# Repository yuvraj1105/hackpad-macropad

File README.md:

# hackpad-macropad
A compact, customizable macropad designed for productivity, shortcuts, and everyday workflow automation. HackPad provides programmable keys that can be mapped to custom shortcuts, commands, macros, and applications, making repetitive tasks faster and more convenient.

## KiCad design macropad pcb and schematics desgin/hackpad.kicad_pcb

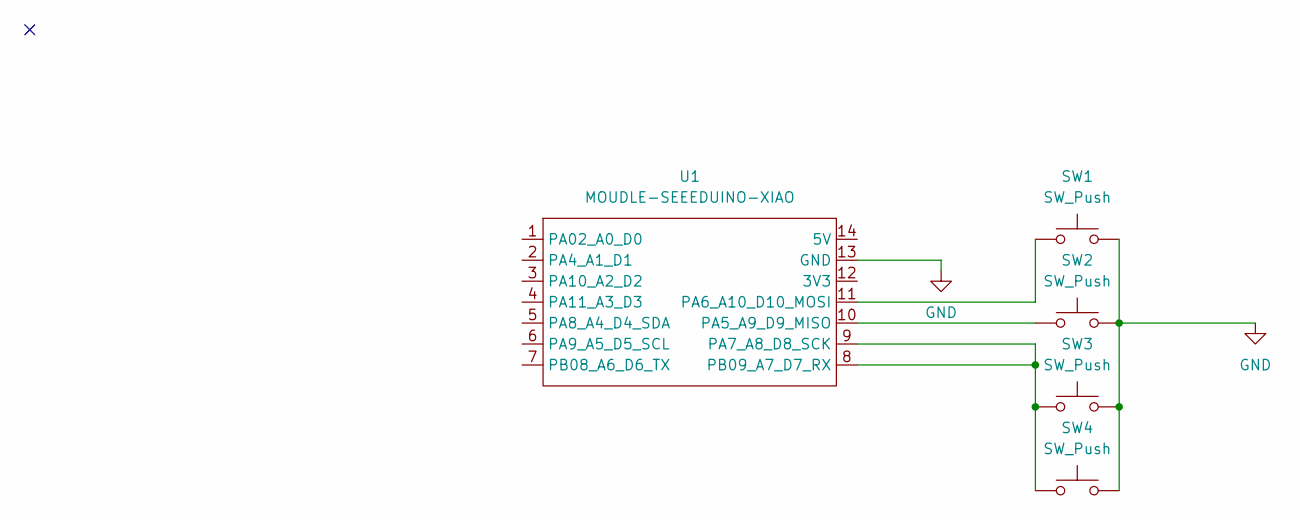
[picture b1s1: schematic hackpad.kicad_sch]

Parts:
SW1, SW2, SW3, SW4: SW_Push; SW_Cherry_MX_1.00u_PCB
U1: MOUDLE-SEEEDUINO-XIAO; XIAO-Generic-Hybrid-14P-2.54-21X17.8MM

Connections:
GND: SW1.2, SW2.2, SW3.2, SW4.2, U1.13 (GND)
unnamed: SW2.1, U1.10 (PA5_A9_D9_MISO)
unnamed: SW1.1, U1.11 (PA6_A10_D10_MOSI)
unnamed: SW3.1, SW4.1, U1.8 (PB09_A7_D7_RX), U1.9 (PA7_A8_D8_SCK)

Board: 2 copper layers, 5 parts (1 on the bottom side), 4 nets, no tracks yet.
